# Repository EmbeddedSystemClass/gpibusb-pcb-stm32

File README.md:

GPIBUSB Adapter PCB
===================

This repository is a clone of www.github.com/Galvant/gpibusb-pcb . It utilizes an STM32 microcontroller instead of a PIC and adds ESD protection circuitry.

> This repository contains the KiCAD PCB project files for the GPIBUSB Adapter project.

> The associated firmware project can be found on GitHub at www.github.com/Galvant/gpibusb-firmware

> Pre-assembled boards can be found at www.galvant.ca

About
-----

Many pieces of test & measurement equipment feature a connectivity port labelled "GPIB" which stands
for General Purpose Interface Bus. On some equipment this can also be labelled as "HPIB" after the 
company that originally invented it.

Commercial USB to GPIB adapters contain a lot of features and functionality, but are also very 
expensive ($500+ new). This is well out of price range for most hobbyists, as well as plenty of engineers
and scientists. A lot of people don't need all of the advanced GPIB communication functionality; some
are just looking to download multimeter readings or oscilloscope waveforms to their PC. This firmware
project aims to implement as much GPIB communication functionality as possible, while still remaining
accessable.

Another limitation of your typical USB to GPIB adapter is the development environment restriction
due to the required drivers. For example, these vendors only provide Linux drivers for Red 
Hat-based distributions, but these drivers do not include MATLAB bindings! Instead of having to deal
with all sorts of GPIB and VISA driver stuff, this GPIBUSB adapter presents itself to the attached PC
as a serial port, allowing a wide variety of operating systems and development environments to utilize
it. So although this means that this adapter is NOT a drop in replacement for convential ones, this
flexability is desired by many.

Related Repos
-------------

See the following repos for more information

Firmware: https://www.github.com/Galvant/gpibusb-firmware

Docs: https://www.github.com/Galvant/gpibusb-documentation

Bootloader: https://www.github.com/Galvant/gpibusb-bootloader

Firmware Compatibility
----------------------

>Here hardware revisions (left) are listed with their compatible software versions (right). The hardware
revision is marked on the silkscreen on the adapter PCB.

>revB/rev2: v1 - v3

>rev3 family (ie 3.1, 3.2): v4

License
-------

This work is released under the Creative Commons Attribution-Sharealike 3.0 license.
See http://creativecommons.org/licenses/by-sa/3.0/ or the included license/LICENSE.TXT file for more information.

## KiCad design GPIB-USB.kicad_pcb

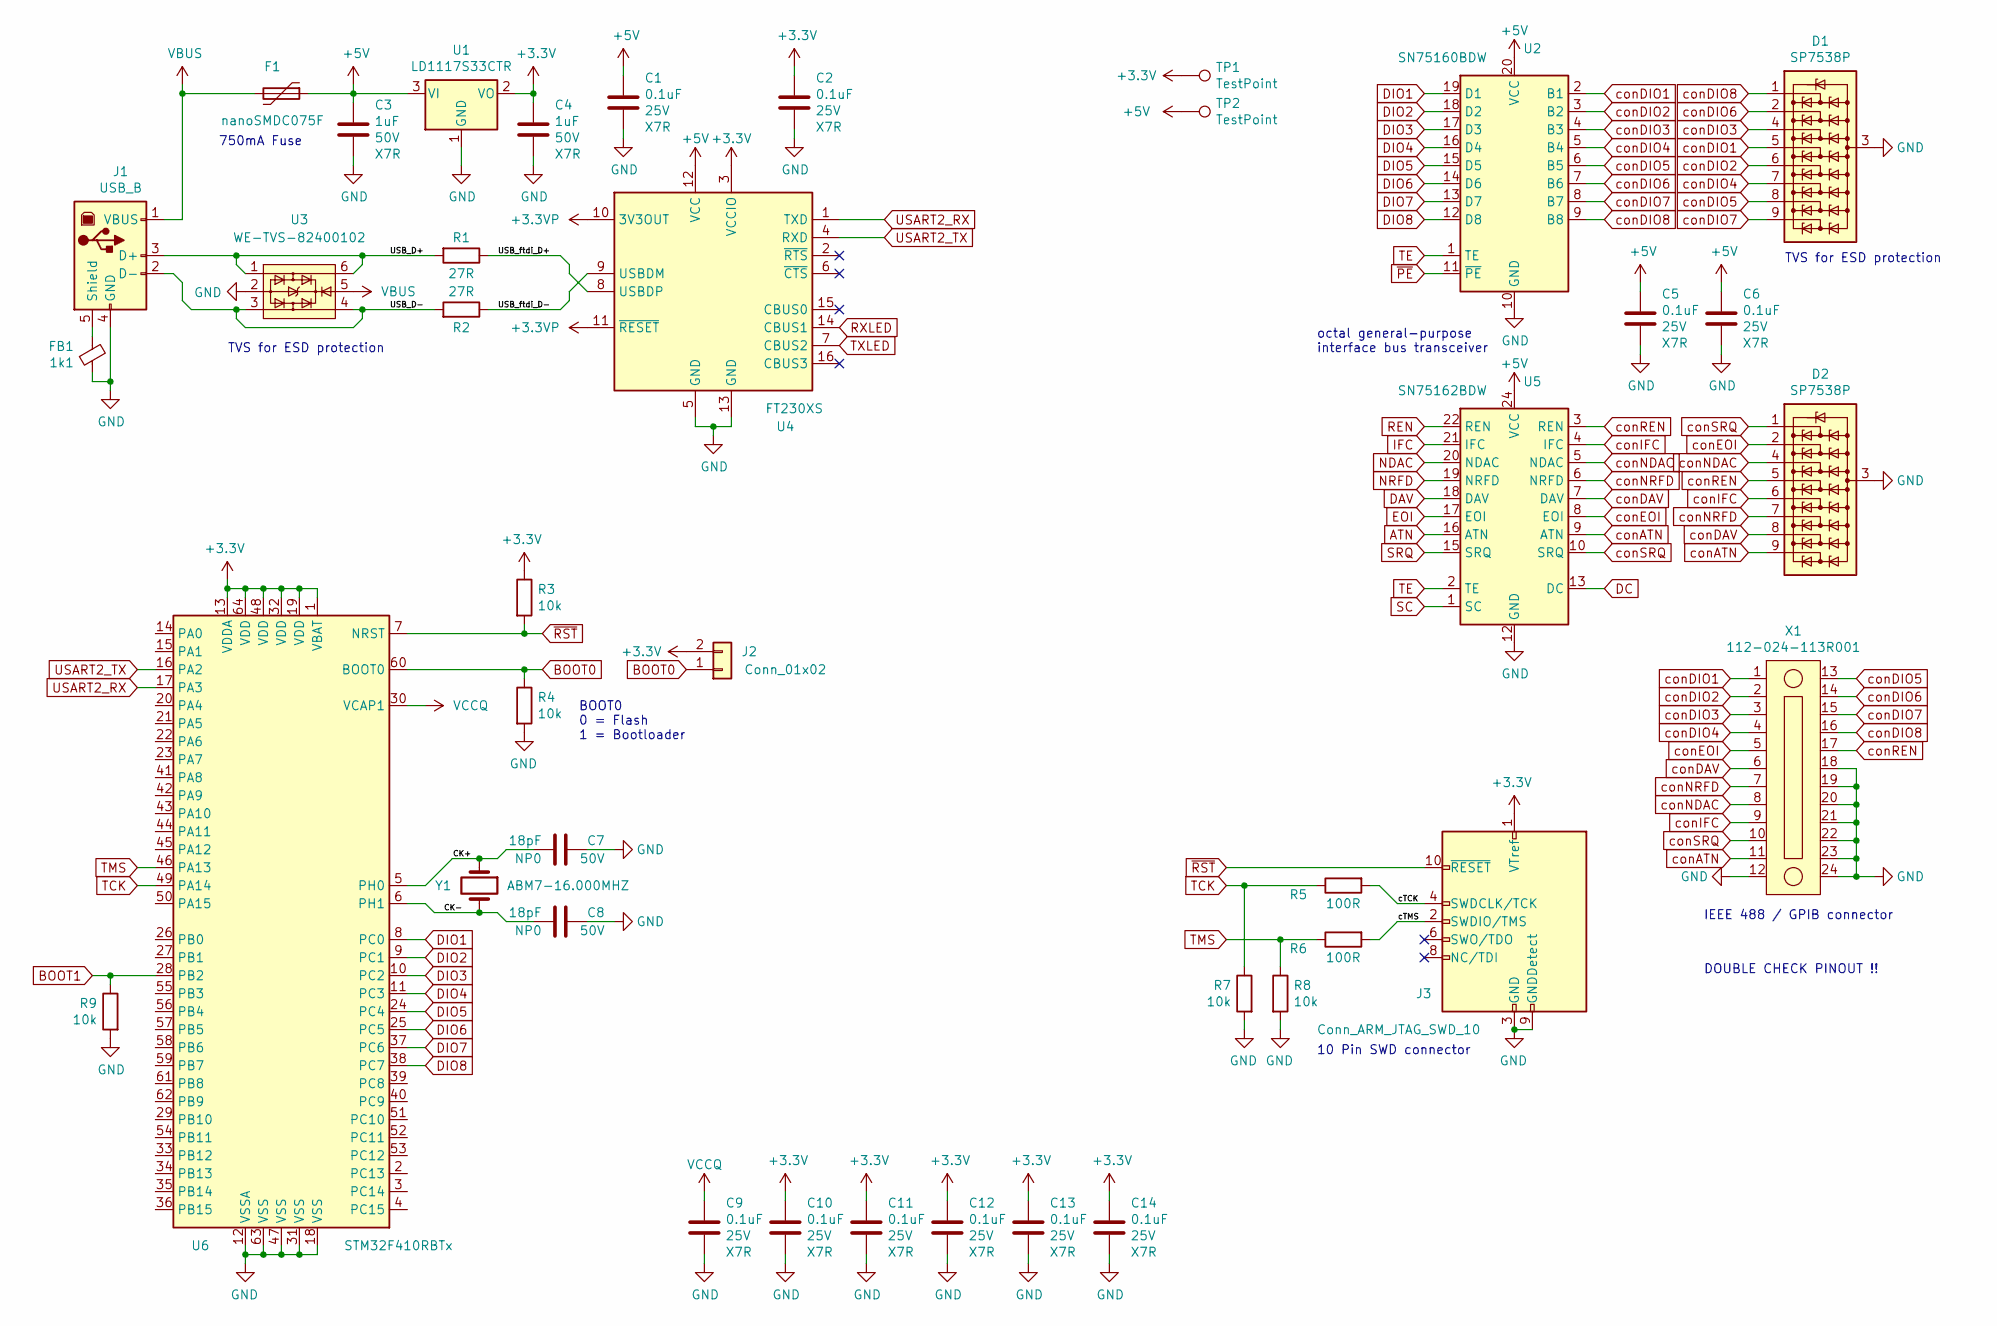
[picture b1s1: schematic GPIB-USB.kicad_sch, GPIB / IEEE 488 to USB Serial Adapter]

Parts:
C1, C2, C5, C6, C9, C10, C11, C12, C13, C14: 0.1uF; C_0805_2012Metric; Voltage 25V
C3, C4: 1uF; C_0805_2012Metric; Voltage 50V
C7, C8: 18pF; C_0603_1608Metric; Voltage 50V
D1, D2: SP7538P; UDFN-9_1.0x3.8mm_P0.5mm
F1: nanoSMDC075F; R_1206_3216Metric
FB1: 1k1; R_0805_2012Metric
J1: USB_B; USB_B_OST_USB-B1HSxx_Horizontal
J2: Conn_01x02; PinHeader_1x02_P2.54mm_Vertical
J3: Conn_ARM_JTAG_SWD_10; PinHeader_2x05_P1.27mm_Vertical_SMD
R1, R2: 27R; R_0805_2012Metric
R3, R4, R7, R8, R9: 10k; R_0805_2012Metric
R5, R6: 100R; R_0805_2012Metric
TP1, TP2: TestPoint; TestPoint_Loop_D1.80mm_Drill1.0mm_Beaded
U1: LD1117S33CTR; SOT-223-3_TabPin2
U2: SN75160BDW; SOIC-20W_7.5x12.8mm_P1.27mm
U3: WE-TVS-82400102; SOT-23-6
U4: FT230XS; SSOP-16_3.9x4.9mm_P0.635mm
U5: SN75162BDW; SOIC-24W_7.5x15.4mm_P1.27mm
U6: STM32F410RBTx; LQFP-64_10x10mm_P0.5mm
X1: 112-024-113R001
Y1: ABM7-16.000MHZ; Crystal_SMD_Abracon_ABM7-2Pin_6.0x3.5mm

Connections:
+3.3VP: U4.10 (3V3OUT), U4.11 (~RESET)
+3V3: C2.1, C4.1, C10.1, C11.1, C12.1, C13.1, C14.1, J2.2, J3.1 (VTref), R3.1, TP1.1, U1.2 (VO), U4.3 (VCCIO), U6.1 (VBAT), U6.13 (VDDA), U6.19 (VDD), U6.32 (VDD), U6.48 (VDD), U6.64 (VDD)
+5V: C1.1, C3.1, C5.1, C6.1, F1.1, TP2.1, U1.3 (VI), U2.20 (VCC), U4.12 (VCC), U5.24 (VCC)
/CK+: C7.1, U6.5 (PH0), Y1.1
/CK-: C8.1, U6.6 (PH1), Y1.2
/USB_D+: J1.3 (D+), R1.2, U3.1, U3.6
/USB_D-: J1.2 (D-), R2.2, U3.3, U3.4
/USB_ftdi_D+: R1.1, U4.8 (USBDP)
/USB_ftdi_D-: R2.1, U4.9 (USBDM)
/cTCK: J3.4 (SWDCLK/TCK), R5.2
/cTMS: J3.2 (SWDIO/TMS), R6.2
ATN: U5.16 (ATN)
BOOT0: J2.1, R4.1, U6.60 (BOOT0)
BOOT1: R9.1, U6.28 (PB2)
DAV: U5.18 (DAV)
DC: U5.13 (DC)
DIO1: U2.19 (D1), U6.8 (PC0)
DIO2: U2.18 (D2), U6.9 (PC1)
DIO3: U2.17 (D3), U6.10 (PC2)
DIO4: U2.16 (D4), U6.11 (PC3)
DIO5: U2.15 (D5), U6.24 (PC4)
DIO6: U2.14 (D6), U6.25 (PC5)
DIO7: U2.13 (D7), U6.37 (PC6)
DIO8: U2.12 (D8), U6.38 (PC7)
EOI: U5.17 (EOI)
GND: C1.2, C2.2, C3.2, C4.2, C5.2, C6.2, C7.2, C8.2, C9.2, C10.2, C11.2, C12.2, C13.2, C14.2, D1.3 (A), D2.3 (A), FB1.1, J1.4 (GND), J3.3 (GND), J3.5 (GND), J3.9 (GNDDetect), R4.2, R7.2, R8.2, R9.2, U1.1 (GND), U2.10 (GND), U3.2, U4.5 (GND), U4.13 (GND), U5.12 (GND), U6.12 (VSSA), U6.18 (VSS), U6.31 (VSS), U6.47 (VSS), U6.63 (VSS), X1.12, X1.18, X1.19, X1.20, X1.21, X1.22, X1.23, X1.24
IFC: U5.21 (IFC)
NDAC: U5.20 (NDAC)
NRFD: U5.19 (NRFD)
unnamed: FB1.2, J1.5 (Shield)
REN: U5.22 (REN)
RXLED: U4.14 (CBUS1)
SC: U5.1 (SC)
SRQ: U5.15 (SRQ)
TCK: R5.1, R7.1, U6.49 (PA14)
TE: U2.1 (TE), U5.2 (TE)
TMS: R6.1, R8.1, U6.46 (PA13)
TXLED: U4.7 (CBUS2)
USART2_RX: U4.1 (TXD), U6.17 (PA3)
USART2_TX: U4.4 (RXD), U6.16 (PA2)
VBUS: F1.2, J1.1 (VBUS), U3.5
VCCQ: C9.1, U6.30 (VCAP1)
conATN: D2.9 (K8), U5.9 (ATN), X1.11
conDAV: D2.8 (K7), U5.7 (DAV), X1.6
conDIO1: D1.5 (K4), U2.2 (B1), X1.1
conDIO2: D1.6 (K5), U2.3 (B2), X1.2
conDIO3: D1.4 (K3), U2.4 (B3), X1.3
conDIO4: D1.7 (K6), U2.5 (B4), X1.4
conDIO5: D1.8 (K7), U2.6 (B5), X1.13
conDIO6: D1.2 (K2), U2.7 (B6), X1.14
conDIO7: D1.9 (K8), U2.8 (B7), X1.15
conDIO8: D1.1 (K1), U2.9 (B8), X1.16
conEOI: D2.2 (K2), U5.8 (EOI), X1.5
conIFC: D2.6 (K5), U5.4 (IFC), X1.9
conNDAC: D2.4 (K3), U5.5 (NDAC), X1.8
conNRFD: D2.7 (K6), U5.6 (NRFD), X1.7
conREN: D2.5 (K4), U5.3 (REN), X1.17
conSRQ: D2.1 (K1), U5.10 (SRQ), X1.10
~PE~: U2.11 (~PE)
~RST~: J3.10 (~RESET~), R3.2, U6.7 (NRST)

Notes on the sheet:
750mA Fuse
TVS for ESD protection
BOOT0 0 = Flash 1 = Bootloader
octal general-purpose interface bus transceiver
10 Pin SWD connector
IEEE 488 / GPIB connector
DOUBLE CHECK PINOUT !!

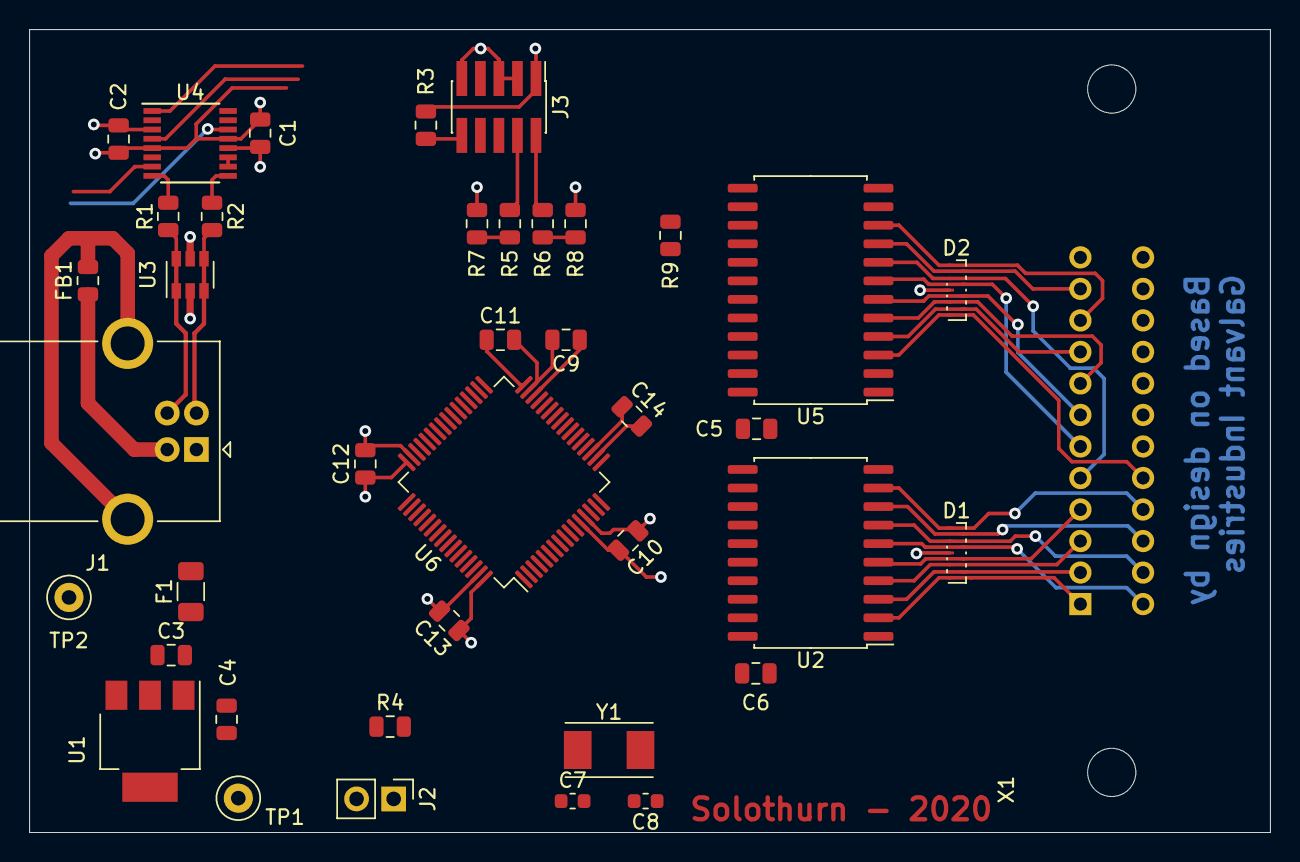
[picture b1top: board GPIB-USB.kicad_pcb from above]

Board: 2 copper layers, 85.0 x 55.0 mm, 40 parts (0 on the bottom side), 47 nets.

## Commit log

2020-08-22 modified gitignore
2020-08-31 update?
2021-05-31 upgrade to Kicad6
2021-05-31 update to kicad6
